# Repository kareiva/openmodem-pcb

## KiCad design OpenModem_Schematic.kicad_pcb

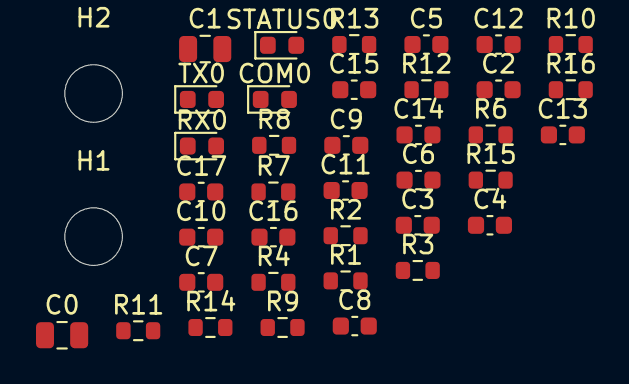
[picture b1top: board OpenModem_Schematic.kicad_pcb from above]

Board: 2 copper layers, 39 parts (0 on the bottom side), 8 nets, no tracks yet.

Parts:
C0, C1: 10uF; C_0805_2012Metric
C2, C4, C5, C7, C12: 100nF; C_0603_1608Metric
C3, C6, C8, C9, C10, C11, C17: 1uF; C_0603_1608Metric
C13, C14: 47pF; C_0603_1608Metric
C15, C16: 30pF; C_0603_1608Metric
COM0: LEDCHIP-LED0603; LED_0603_1608Metric
H1, H2: MOUNT-HOLE3.2; MountingHole_3.2mm_M3
R1, R2: 27; R_0603_1608Metric
R3, R4, R12, R14: 270; R_0603_1608Metric
R6, R7, R8, R15: 10k; R_0603_1608Metric
R9, R10: 100k; R_0603_1608Metric
R11, R16: 2k2; R_0603_1608Metric
R13: 1k; R_0603_1608Metric
RX0: LEDCHIP-LED0603; LED_0603_1608Metric
STATUS0: LEDCHIP-LED0603; LED_0603_1608Metric
TX0: LEDCHIP-LED0603; LED_0603_1608Metric

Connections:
/5V_REG: C1.1, C2.1, C3.1, C5.1, C6.1, C7.1, C8.1, R6.2
/AREF: C10.2, R8.2, R9.1
/DAC_REF: C9.2, R7.2
/GND: C0.2, C1.2, C2.2, C3.2, C4.1, C5.2, C6.2, C7.2, C8.2, C9.1, C10.1, C13.1, C14.1, C15.2, C16.2, R10.1, R15.1
/PA0: C11.2, R9.2, R10.2
/RESET: C12.1, R6.1
unnamed: C13.2, R2.1
unnamed: C14.2, R1.1

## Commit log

2022-06-09 WIP: unmatched complex footprints
